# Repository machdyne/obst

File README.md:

# Obst Computer

Obst is an FPGA computer designed by Lone Dynamics Corporation.

This repo will contain schematics, PCB layouts, pinouts, a 3D-printable case, example gateware and documentation.

Find more information on the [Obst product page](https://machdyne.com/product/obst-computer/).

## Programming Obst

Obst has a JTAG interface and ships with a [DFU bootloader](https://github.com/machdyne/tinydfu-bootloader) that allows the included flash [MMOD](https://machdyne.com/product/mmod) to be programmed over the USB-C port.

### DFU

The DFU bootloader is available for 5 seconds after power-on, issuing a DFU command during this period will stop the boot process until the DFU device is detached. If no command is received the boot process will continue and the user gateware will be loaded.

Install [dfu-util](http://dfu-util.sourceforge.net) (Debian/Ubuntu):

```
$ sudo apt install dfu-util
```

Update the user gateware on the flash MMOD:

```
$ sudo dfu-util -a 0 -D image.bit
```

Detach the DFU device and continue the boot process:

```
$ sudo dfu-util -a 0 -e
```

It is possible to update the bootloader itself using DFU but you shouldn't attempt this unless you have a JTAG programmer (or another method to program the MMOD) available, in case you need to restore the bootloader.

### JTAG

These examples assume you're using a "USB Blaster" JTAG cable, see the header pinout below. You will need to have [openFPGALoader](https://github.com/trabucayre/openFPGALoader) installed.

Program the configuration SRAM:

```
openFPGALoader -c usb-blaster image.bit
```

Program the flash MMOD:

```
openFPGALoader -f -c usb-blaster images/bootloader/tinydfu_obst.bit
```

## Blinky 

Building the blinky example requires [Yosys](https://github.com/YosysHQ/yosys), [nextpnr-ecp5](https://github.com/YosysHQ/nextpnr) and [Project Trellis](https://github.com/YosysHQ/prjtrellis).

Assuming they are installed, you can simply type `make` to build the gateware, which will be written to output/blinky.bin. You can then use [openFPGALoader](https://github.com/trabucayre/openFPGALoader) or dfu-util to write the gateware to the device.

## Zucker SOC

Obst can be used with [Zucker SOC](https://github.com/machdyne/zucker).

## JTAG Header

The 3.3V JTAG header can be used to program the FPGA SRAM as well as the MMOD flash memory. It can also be used to provide power (5V) to the board.

```
2 4 6
1 3 5
```

| Pin | Signal |
| --- | ------ |
| 1 | TCK |
| 2 | TDI |
| 3 | TDO |
| 4 | TMS |
| 5 | 5V0 |
| 6 | GND |

## Board Revisions

| Revision | Notes |
| -------- | ----- |
| V0A | Initial production version |
| V0B | Latest production version |

## License

The contents of this repo are released under the [Lone Dynamics Open License](LICENSE.md) with the following exceptions:

- The KiCad design files contain parts of the [kicad-pmod](https://github.com/mithro/kicad-pmod) library which is released under the [Apache License, Version 2.0](https://www.apache.org/licenses/LICENSE-2.0.html).

- The KiCad design files may contain symbols and footprints released under other licenses; please contact us if we've failed to give proper attribution.

Note: You can use these designs for commercial purposes but we ask that instead of producing exact clones, that you either replace our trademarks and logos with your own or add your own next to ours.

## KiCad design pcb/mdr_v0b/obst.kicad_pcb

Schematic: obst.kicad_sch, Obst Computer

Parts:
C1, C2, C3, C4, C5, C6, C7, C9, C10, C32: 220nF; C_0603_1608Metric
C8, C11, C12, C13: 1uF; C_0603_1608Metric
C14, C15, C16, C33, C34, C35, C36: 4.7uF; C_0603_1608Metric
C17, C19, C21, C23, C25, C26, C29, C30: 100nF; C_0603_1608Metric
C18, C20, C22, C24: 2.2uF; C_0603_1608Metric
C27, C28, C31, C41: 10uF; C_0603_1608Metric
C37, C38: 10pF; C_0603_1608Metric
C39, C40, C42, C43: 22uF; C_0603_1608Metric
D2: LED_RGB_ANODE; LED_RGB_0606_CHANZON
FB1, FB2: Ferrite_Bead; R_0603_1608Metric
H1, H2, H3, H4: MountingHole_Pad; MountingHole_3.2mm_M3_Pad
J1: TYPE-C-31-M-12-FIXED; USB_C_Receptacle_HRO_TYPE-C-31-M-12-BIG-PADS; PARTREV A
J2: USB_A_Stacked; USB_A_Wuerth_61400826021_Horizontal_Stacked
J3: MICROSD; SDCARD
J4: AudioJack4; Jack_3.5mm_PJ320D_Horizontal
J5: Conn_02x03_Odd_Even; PinHeader_2x03_P2.54mm_Vertical
L1, L2: INDUCTOR; L_0805_2012Metric
MMOD1: PMOD-Device-x1-Type-2-SPI; MMOD_Host_Socket
PMOD1, PMOD2: PMOD-Device-x2-Type-1A-GPIO; PMOD_2x06_HOST
Q1, Q2, Q3, Q4: BSS138; SOT-323_SC-70
R2, R3, R12, R13, R14, R15: 4K7; R_0603_1608Metric
R4, R9: 5K1; R_0603_1608Metric
R5, R42, R51, R64, R69: 1K; R_0603_1608Metric
R6, R7, R20, R21, R22, R23: 22R; R_0603_1608Metric
R8: 51R; R_0603_1608Metric
R10, R11, R24, R27, R28, R29, R30, R33, R34, R35: 10K; R_0603_1608Metric
R16, R17, R18, R19: 15K; R_0603_1608Metric
R25, R26, R31, R32, R46, R52, R56, R57, R65, R70, R72, R73: 100R; R_0603_1608Metric
R36, R41, R48, R49, R50, R63, R68: 536R; R_0603_1608Metric
R37, R38, R39, R45: 20K; R_0603_1608Metric
R40, R53, R55, R67: 270R; R_0603_1608Metric
R43: 2K2; R_0603_1608Metric
R44, R58: 1K5; R_0603_1608Metric
R47: 33R; R_0603_1608Metric
R54, R66, R71: 27R; R_0603_1608Metric
R59: 100K; R_0603_1608Metric
R60: 120K; R_0603_1608Metric
R61: 200K; R_0603_1608Metric
R62: 44.2K; R_0603_1608Metric
TP1: TP_PWR5V0; TestPoint_THTPad_D1.0mm_Drill0.5mm
TP2: TP_PWR3V3; TestPoint_THTPad_D1.0mm_Drill0.5mm
TP3: TP_PWR1V1; TestPoint_THTPad_D1.0mm_Drill0.5mm
U1: Lattice_ECP_FPGA_ECP5U_45_CABGA256; BGA-256_14.0x14.0mm_Layout16x16_P0.8mm_Ball0.45mm_Pad0.32mm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
U2, U4: IS61WV51216EDBLL; TSOP-II-44_10.16x18.41mm_P0.8mm
U3, U5: PS2; MINI-DIN-6-FULL-SHIELD
U6: MIC5504-2.5YM5; SOT-23-5
U8, U9: TLV62568DDC; SOT-23-6
VGA1: DB15_Female_MountingHoles; DSUB-15-HD_Female_Horizontal_P2.29x1.98mm_EdgePinOffset3.03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
Y1: KC2016Z48.0000C1KX00; OSC_KC2016Z13.5600C1KX00; PARTREV November 2020

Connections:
/AUDIO_L: R72.1, U1.J2 (PL32B/-/PCLKC7_1/HS/LDQ29)
/AUDIO_LC: C27.2, J4.T
/AUDIO_R: R73.1, U1.J1 (PL32A/+/PCLKT7_1/HS/LDQ29)
/AUDIO_RC: C31.2, J4.R1
/CLK48: U1.A7 (PT38A/+/PCLKT0_0), Y1.3 (OUTPUT)
/CSPI_MISO: MMOD1.3 (MISO), R11.2, U1.T7 (PB11A/+/D1/MISO/IO1)
/CSPI_MOSI: MMOD1.2 (MOSI), R10.2, U1.T8 (PB11B/-/D0/MOSI/IO0)
/CSPI_SCK: MMOD1.4 (SCK), R5.2, U1.N9 (CCLK/MCLK/SCK)
/CSPI_SS: MMOD1.1 (SS), U1.N8 (PB15A/+/HOLDN/DI/BUSY/CSSPIN/CEN)
/DONE: U1.P9 (DONE)
/INITN: R2.2, U1.T9 (INITN)
/JTAG_TCK: J5.1, R15.1, U1.T10 (TCK)
/JTAG_TDI: J5.2, R12.2, U1.R11 (TDI)
/JTAG_TDO: J5.3, R13.2, U1.M10 (TDO)
/JTAG_TMS: J5.4, R14.2, U1.T11 (TMS)
/LED_B: R49.1, U1.B11 (PT58A/+)
/LED_G: R36.1, U1.A11 (PT71A/+)
/LED_R: R48.1, U1.C12 (PT74B/-)
/PMOD_A1: PMOD1.1 (IOA0), U1.E5 (PT13A/+)
/PMOD_A2: PMOD1.2 (IOA1), U1.D4 (PT9B/-)
/PMOD_A3: PMOD1.3 (IOA2), U1.B5 (PT15B/-)
/PMOD_A4: PMOD1.4 (IOA3), U1.C6 (PT31A/+)
/PMOD_A7: PMOD1.7 (IOB0), U1.E4 (PT9A/+)
/PMOD_A8: PMOD1.8 (IOB1), U1.C4 (PT11A/+)
/PMOD_A9: PMOD1.9 (IOB2), U1.B6 (PT31B/-)
/PMOD_A10: PMOD1.10 (IOB3), U1.D6 (PT20B/-)
/PMOD_B1: PMOD2.1 (IOA0), U1.C8 (PT44A/+/PCLKT1_0)
/PMOD_B2: PMOD2.2 (IOA1), U1.B9 (PT47A/+/GR_PCLK1_0)
/PMOD_B3: PMOD2.3 (IOA2), U1.A10 (PT51B/-)
/PMOD_B4: PMOD2.4 (IOA3), U1.C10 (PT53B/-)
/PMOD_B7: PMOD2.7 (IOB0), U1.B8 (PT44B/-/PCLKC1_0)
/PMOD_B8: PMOD2.8 (IOB1), U1.A9 (PT51A/+)
/PMOD_B9: PMOD2.9 (IOB2), U1.B10 (PT53A/+)
/PMOD_B10: PMOD2.10 (IOB3), U1.D10 (PT56A/+)
/PROGRAMN: R3.2, R8.2, U1.R9 (PROGRAMN)
/PS2A_CLK: Q2.2 (S), R28.2, U1.L2 (PL35B/-/PCLKC6_1/HS/LDQ41)
/PS2A_CLK5V: Q2.3 (D), R26.1, R29.2
/PS2A_DAT: Q1.2 (S), R24.2, U1.L1 (PL35A/+/PCLKT6_1/HS/LDQ41)
/PS2A_DAT5V: Q1.3 (D), R25.1, R27.2
/PS2B_CLK: Q4.2 (S), R34.2, U1.L4 (PL38C/+/GR_PCLK6_1/LDQ41)
/PS2B_CLK5V: Q4.3 (D), R32.1, R35.2
/PS2B_DAT: Q3.2 (S), R30.2, U1.L3 (PL41C/+/LDQ41)
/PS2B_DAT5V: Q3.3 (D), R31.1, R33.2
/PWR1V1: C3.2, C5.2, C10.2, C12.2, C13.2, C15.2, C37.1, C39.1, C40.1, C42.1, L1.2, R59.1, TP3.1, U1.G6 (VCC[6]), U1.G7 (VCC[6]), U1.G9 (VCC[6]), U1.L8 (VCC[6]), U1.L9 (VCC[6]), U1.L10 (VCC[6])
/PWR1V1EN: R58.2, U8.1 (EN), U9.5 (PG)
/PWR2V5: C4.2, C32.2, C34.1, U1.G11 (VCCAUX[2]), U1.L7 (VCCAUX[2]), U6.5 (VOUT)
/PWR3V3: C1.2, C2.2, C6.2, C7.2, C8.2, C9.2, C11.2, C17.2, C18.2, C19.2, C20.2, C21.2, C22.2, C23.2, C24.2, C25.1, C28.1, C29.1, C33.1, C38.1, C41.1, C43.1, D2.1 (A), J3.4 (VDD), L2.2, MMOD1.6 (VCC), PMOD1.6 (VCC), PMOD1.12 (VCC), PMOD2.6 (VCC), PMOD2.12 (VCC), Q1.1 (G), Q2.1 (G), Q3.1 (G), Q4.1 (G), R2.1, R3.1, R5.1, R10.1, R11.1, R12.1, R13.1, R14.1, R24.1, R28.1, R30.1, R34.1, R37.1, R38.1, R39.1, R45.1, R61.1, TP2.1, U1.F6 (VCCIO0[2]), U1.F7 (VCCIO0[2]), U1.F10 (VCCIO1[2]), U1.F11 (VCCIO1[2]), U1.H6 (VCCIO7[2]), U1.H7 (VCCIO7[2]), U1.H11 (VCCIO2[2]), U1.J6 (VCCIO6[2]), U1.J7 (VCCIO6[2]), U1.J11 (VCCIO2[2]), U1.K11 (VCCIO3[2]), U1.L6 (VCCIO8), U1.L11 (VCCIO3[2]), U1.P10 (CFG_1), U2.11 (VDD1), U2.33 (VDD2), U4.11 (VDD1), U4.33 (VDD2), U6.1 (VIN), U6.3 (EN), Y1.1 (INH), Y1.4 (VCC)
/PWR5V0: C14.1, C16.1, C35.1, C36.1, FB1.1, FB2.1, J5.5, R27.1, R29.1, R33.1, R35.1, R58.1, TP1.1, U3.4 (VCC), U5.4 (VCC), U8.4 (VIN), U9.1 (EN), U9.4 (VIN)
/RESET: R8.1, U1.M8 (PB15B/-/DOUT/CSON)
/SD_MISO: J3.7 (DAT0), R45.2, U1.B4 (PT11B/-)
/SD_MOSI: J3.3 (CMD), R38.2, U1.B3 (PT4B/-/ULC_GPLL1C_IN)
/SD_SCK: J3.5 (CLK), R39.2, U1.A3 (PT6A/+)
/SD_SS: J3.2 (DAT3/CD), R37.2, U1.A2 (PT4A/+/ULC_GPLL1T_IN)
/SRAM0_CS: U1.G12 (PR20A/+/HS/RDQ17), U4.6 (~CS)
/SRAM0_D0: U1.F12 (PR17D/-/RDQ17), U4.7 (D0)
/SRAM0_D1: U1.E14 (PR14C/+/RDQ17), U4.8 (D1)
/SRAM0_D2: U1.K15 (PR32D/-/PCLKC2_0/RDQ29), U4.9 (D2)
/SRAM0_D3: U1.K16 (PR32C/+/PCLKT2_0/RDQ29), U4.10 (D3)
/SRAM0_D4: U1.J15 (PR32B/-/PCLKC2_1/HS/RDQ29), U4.13 (D4)
/SRAM0_D5: U1.J16 (PR32A/+/PCLKT2_1/HS/RDQ29), U4.14 (D5)
/SRAM0_D6: U1.H14 (PR23D/-/RDQ29), U4.15 (D6)
/SRAM0_D7: U1.H15 (PR29B/-/HS/RDQSN29), U4.16 (D7)
/SRAM0_D8: U1.G15 (PR23B/-/HS/RDQ29), U4.29 (D8)
/SRAM0_D9: U1.F16 (PR23A/+/HS/RDQ29), U4.30 (D9)
/SRAM0_D10: U1.F15 (PR20C/+/RDQ17), U4.31 (D10)
/SRAM0_D11: U1.E16 (PR20D/-/RDQ17), U4.32 (D11)
/SRAM0_D12: U1.E15 (PR17B/-/HS/RDQSN17), U4.35 (D12)
/SRAM0_D13: U1.D16 (PR17A/+/HS/RDQS17), U4.36 (D13)
/SRAM0_D14: U1.C14 (PR11C/+/RDQ17), U4.37 (D14)
/SRAM0_D15: U1.C16 (PR14A/+/HS/RDQ17), U4.38 (D15)
/SRAM0_LB: U1.C15 (PR14B/-/HS/RDQ17), U4.39 (~LB)
/SRAM0_OE: U1.B15 (PR11B/-/URC_GPLL0C_IN/HS/RDQ17), U4.41 (~OE)
/SRAM0_UB: U1.B16 (PR11A/+/URC_GPLL0T_IN/HS/RDQ17), U4.40 (~UB)
/SRAM0_WE: U1.G16 (PR29A/+/GR_PCLK2_1/HS/RDQS29), U4.17 (~WE)
/SRAM1_CS: U1.L12 (PR38D/-/RDQ41), U2.6 (~CS)
/SRAM1_D0: U1.L13 (PR38C/+/GR_PCLK3_1/RDQ41), U2.7 (D0)
/SRAM1_D1: U1.L14 (PR41C/+/RDQ41), U2.8 (D1)
/SRAM1_D2: U1.M13 (PR44C/+/RDQ41), U2.9 (D2)
/SRAM1_D3: U1.P11 (PR68C/+/LRC_GPLL0T_IN/RDQ65), U2.10 (D3)
/SRAM1_D4: U1.R12 (PR65A/+/HS/RDQS65), U2.13 (D4)
/SRAM1_D5: U1.T13 (PR65B/-/HS/RDQSN65), U2.14 (D5)
/SRAM1_D6: U1.R13 (PR62C/+/RDQ65), U2.15 (D6)
/SRAM1_D7: U1.T14 (PR62D/-/RDQ65), U2.16 (D7)
/SRAM1_D8: U1.T15 (PR59D/-/RDQ65), U2.29 (D8)
/SRAM1_D9: U1.R15 (PR59C/+/RDQ65), U2.30 (D9)
/SRAM1_D10: U1.R16 (PR44B/-/VREF1_3/HS/RDQ41), U2.31 (D10)
/SRAM1_D11: U1.P15 (PR41B/-/HS/RDQSN41), U2.32 (D11)
/SRAM1_D12: U1.P16 (PR44A/+/HS/RDQ41), U2.35 (D12)
/SRAM1_D13: U1.N14 (PR44D/-/RDQ41), U2.36 (D13)
/SRAM1_D14: U1.N16 (PR41A/+/HS/RDQS41), U2.37 (D14)
/SRAM1_D15: U1.L16 (PR35A/+/PCLKT3_1/HS/RDQ41), U2.38 (D15)
/SRAM1_LB: U1.L15 (PR35B/-/PCLKC3_1/HS/RDQ41), U2.39 (~LB)
/SRAM1_OE: U1.M15 (PR35D/-/PCLKC3_0/RDQ41), U2.41 (~OE)
/SRAM1_UB: U1.M16 (PR35C/+/PCLKT3_0/RDQ41), U2.40 (~UB)
/SRAM1_WE: U1.R14 (PR62B/-/HS/RDQ65), U2.17 (~WE)
/SRAM_A0: U1.J14 (PR29C/+/GR_PCLK2_0/RDQ29), U2.1 (A0), U4.1 (A0)
/SRAM_A1: U1.J13 (PR26C/+/RDQ29), U2.2 (A1), U4.2 (A1)
/SRAM_A2: U1.J12 (PR26D/-/RDQ29), U2.3 (A2), U4.3 (A2)
/SRAM_A3: U1.G14 (PR23C/+/VREF1_2/RDQ29), U2.4 (A3), U4.4 (A3)
/SRAM_A4: U1.G13 (PR20B/-/HS/RDQ17), U2.5 (A4), U4.5 (A4)
/SRAM_A5: U1.N13 (PR59A/+/HS/RDQ65), U2.18 (A5), U4.18 (A5)
/SRAM_A6: U1.P14 (PR59B/-/HS/RDQ65), U2.19 (A6), U4.19 (A6)
/SRAM_A7: U1.P13 (PR62A/+/HS/RDQ65), U2.20 (A7), U4.20 (A7)
/SRAM_A8: U1.P12 (PR68D/-/LRC_GPLL0C_IN/RDQ65), U2.21 (A8), U4.21 (A8)
/SRAM_A9: U1.N12 (PR65D/-/RDQ65), U2.22 (A9), U4.22 (A9)
/SRAM_A10: U1.B12 (PT74A/+), U2.23 (A10), U4.23 (A10)
/SRAM_A11: U1.A12 (PT71B/-), U2.24 (A11), U4.24 (A11)
/SRAM_A12: U1.A13 (PT83A/+), U2.25 (A12), U4.25 (A12)
/SRAM_A13: U1.B13 (PT78A/+), U2.26 (A13), U4.26 (A13)
/SRAM_A14: U1.C13 (PT78B/-), U2.27 (A14), U4.27 (A14)
/SRAM_A15: U1.A15 (PT85B/-/URC_GPLL1C_IN), U2.42 (A15), U4.42 (A15)
/SRAM_A16: U1.B14 (PT85A/+/URC_GPLL1T_IN), U2.43 (A16), U4.43 (A16)
/SRAM_A17: U1.A14 (PT83B/-), U2.44 (A17), U4.44 (A17)
/SRAM_A18: U1.D13 (PT80A/+), U2.28 (A18), U4.28 (A18)
/USB1C_DN: J2.2 (D1-), R17.1, R21.2
/USB1C_DP: J2.3 (D1+), R16.1, R20.2
/USB1_DN: R21.1, U1.B2 (PL11B/-/ULC_GPLL0C_IN/HS/LDQ17)
/USB1_DP: R20.1, U1.B1 (PL11A/+/ULC_GPLL0T_IN/HS/LDQ17)
/USB2C_DN: J2.6 (D2-), R19.1, R23.2
/USB2C_DP: J2.7 (D2+), R18.1, R22.2
/USB2_DN: R23.1, U1.C2 (PL14B/-/HS/LDQ17)
/USB2_DP: R22.1, U1.C1 (PL14A/+/HS/LDQ17)
/USB_CONN_DN: J1.A7 (DN1), J1.B7 (DN2), R6.1
/USB_CONN_DP: J1.A6 (DP1), J1.B6 (DP2), R7.1
/USB_DN: R6.2, U1.M2 (PL35D/-/PCLKC6_0/LDQ41)
/USB_DP: R7.2, R44.2, U1.M1 (PL35C/+/PCLKT6_0/LDQ41)
/USB_DP_PU: R44.1, U1.R1 (PL44B/-/VREF1_6/HS/LDQ41)
/VGA_B0: R67.2, U1.N3 (PL44D/-/LDQ41)
/VGA_B1: R68.2, U1.T2 (PL59D/-/LDQ65)
/VGA_B2: R69.2, U1.R2 (PL59C/+/LDQ65)
/VGA_B_CONN: R71.1, VGA1.3
/VGA_G0: R55.2, U1.T4 (PL65B/-/HS/LDQSN65)
/VGA_G1: R63.2, U1.R4 (PL62C/+/LDQ65)
/VGA_G2: R64.2, U1.P4 (PL62A/+/HS/LDQ65)
/VGA_G_CONN: R66.1, VGA1.2
/VGA_HS: R56.2, U1.P2 (PL41B/-/HS/LDQSN41)
/VGA_HS_CONN: R56.1, VGA1.13
/VGA_R0: R53.2, U1.M6 (PL68A/+/HS/LDQ65)
/VGA_R1: R50.2, U1.P6 (PL68C/+/LLC_GPLL0T_IN/LDQ65)
/VGA_R2: R51.2, U1.N6 (PL68B/-/HS/LDQ65)
/VGA_R_CONN: R54.1, VGA1.1
/VGA_VS: R57.2, U1.N1 (PL41A/+/HS/LDQS41)
/VGA_VS_CONN: R57.1, VGA1.14
/VIDEOC: J4.R2, R47.2
/VIDEO_D0: R40.1, U1.G4 (PL20B/-/HS/LDQ17)
/VIDEO_D1: R41.1, U1.G3 (PL23C/+/VREF1_7/LDQ29)
/VIDEO_D2: R42.1, U1.G2 (PL23B/-/HS/LDQ29)
/VIDEO_D3: R43.1, U1.H2 (PL29B/-/HS/LDQSN29)
GND: C1.1, C2.1, C3.1, C4.1, C5.1, C6.1, C7.1, C8.1, C9.1, C10.1, C11.1, C12.1, C13.1, C14.2, C15.1, C16.2, C17.1, C18.1, C19.1, C20.1, C21.1, C22.1, C23.1, C24.1, C25.2, C26.2, C28.2, C29.2, C30.2, C32.1, C33.2, C34.2, C35.2, C36.2, C39.2, C40.2, C41.2, C42.2, C43.2, H1.1, H2.1, H3.1, H4.1, J1.A1 (GND), J1.A12 (GND), J1.B1 (GND), J1.B12 (GND), J1.S1 (SHIELD), J1.S2 (SHIELD), J1.S3 (SHIELD), J1.S4 (SHIELD), J2.4 (GND1), J2.8 (GND2), J2.9 (Shield), J3.6 (VSS), J4.S, J5.6, MMOD1.5 (GND), PMOD1.5 (GND), PMOD1.11 (GND), PMOD2.5 (GND), PMOD2.11 (GND), R4.2, R9.2, R15.2, R16.2, R17.2, R18.2, R19.2, R60.2, R62.2, U1.A1 (GND[27]), U1.A16 (GND[27]), U1.D2 (GND[27]), U1.D15 (GND[27]), U1.F8 (GND[27]), U1.F9 (GND[27]), U1.G8 (GND[27]), U1.G10 (GND[27]), U1.H1 (GND[27]), U1.H8 (GND[27]), U1.H9 (GND[27]), U1.H10 (GND[27]), U1.H16 (GND[27]), U1.J8 (GND[27]), U1.J9 (GND[27]), U1.J10 (GND[27]), U1.K6 (GND[27]), U1.K7 (GND[27]), U1.K8 (GND[27]), U1.K9 (GND[27]), U1.K10 (GND[27]), U1.N2 (GND[27]), U1.N10 (CFG_0), U1.N15 (GND[27]), U1.R10 (CFG_2), U1.T1 (GND[27]), U1.T5 (GND[27]), U1.T12 (GND[27]), U1.T16 (GND[27]), U2.12 (VSS1), U2.34 (VSS2), U3.3 (GND), U4.12 (VSS1), U4.34 (VSS2), U5.3 (GND), U6.2 (GND), U8.2 (GND), U9.2 (GND), VGA1.0 (PAD), VGA1.5, VGA1.6, VGA1.7, VGA1.8, VGA1.10, Y1.2 (CASE_GND)
unnamed: C26.1, C27.1, R72.2
unnamed: C30.1, C31.1, R73.2
unnamed: D2.2 (BK), R49.2
unnamed: D2.4 (GK), R36.2
unnamed: D2.3 (RK), R48.2
unnamed: FB1.2, J1.A4 (VBUS), J1.A9 (VBUS), J1.B4 (VBUS), J1.B9 (VBUS)
unnamed: J1.A5 (CC1), R4.1
unnamed: J1.B5 (CC2), R9.1
unnamed: FB2.2, J2.1 (VBUS1), J2.5 (VBUS2)
unnamed: R40.2, R41.2, R42.2, R43.2, R46.1
unnamed: R46.2, R47.1
unnamed: R50.1, R51.1, R52.2, R53.1
unnamed: R52.1, R54.2
unnamed: R55.1, R63.1, R64.1, R65.2
unnamed: R65.1, R66.2
unnamed: R67.1, R68.1, R69.1, R70.2
unnamed: R70.1, R71.2
unnamed: R26.2, U3.5 (CLK)
unnamed: R25.2, U3.1 (DATA)
unnamed: R32.2, U5.5 (CLK)
unnamed: R31.2, U5.1 (DATA)
unnamed: C37.2, R59.2, R60.1, U8.6 (FB)
unnamed: L1.1, U8.3 (SW)
unnamed: C38.2, R61.2, R62.1, U9.6 (FB)
unnamed: L2.1, U9.3 (SW)

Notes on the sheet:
0.6 * (1 + (100/120)) = 1.099
PS/2
POWER
0.6 * (1 + (200/44.2)) = 3.3149
VGA DAC
MMOD has a 10K pull-up on CSPI_SS
MICROSD
USB DEVICE
AUDIO/VIDEO
USB HOST
MMOD
PMODS
32-BIT SRAM
O B S T

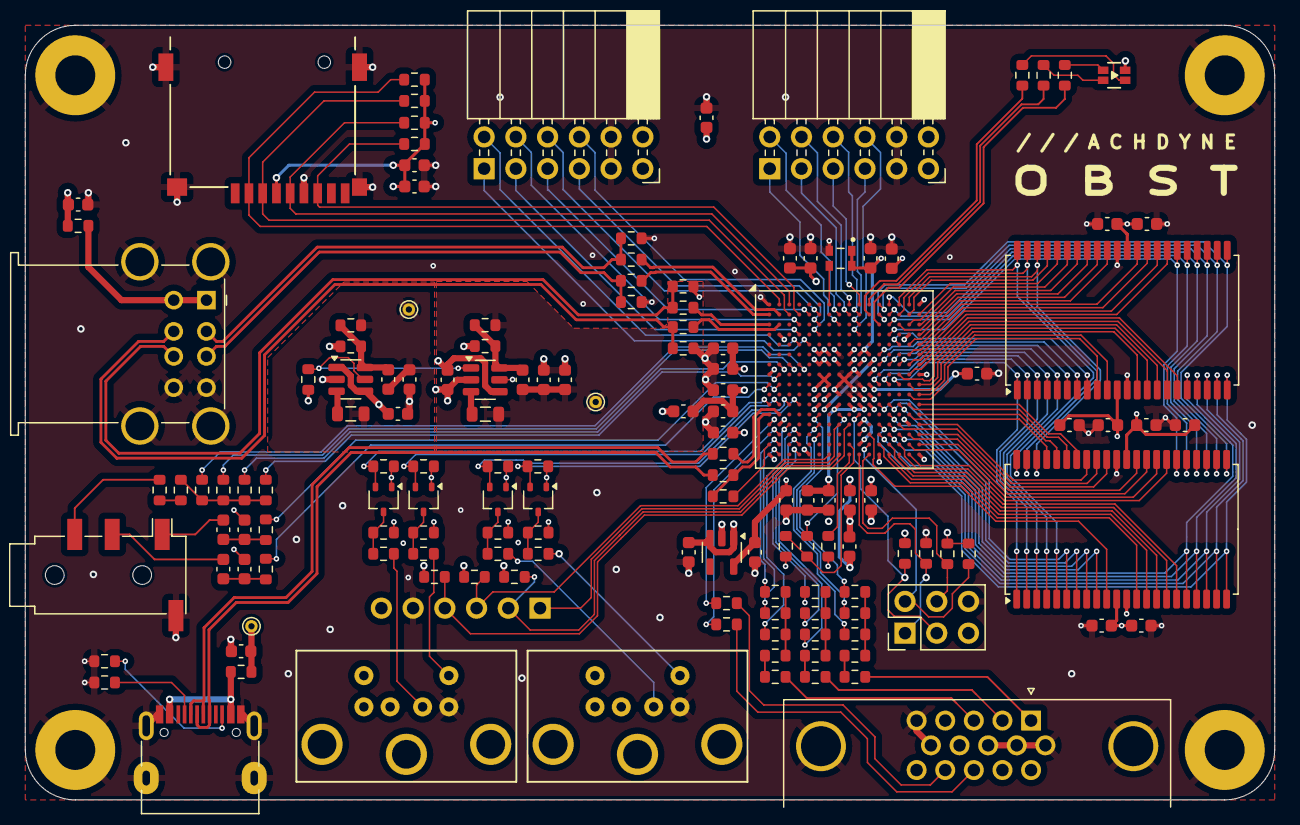
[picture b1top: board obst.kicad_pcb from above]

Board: 4 copper layers, 100.0 x 62.0 mm, 149 parts (1 on the bottom side), 173 nets.

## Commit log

2024-04-24 add render
2024-04-24 add bootloader image
2024-04-24 add blinky
2024-04-24 add constraints
2024-04-26 add case
2024-04-26 update case
2024-09-08 add pmods to lpf
2024-09-08 add audio/video to lpf
2024-09-08 add remaining signals to lpf
2024-10-17 add supports
2026-06-17 add schematics and pcb layout

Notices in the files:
pcb/mdr_v0b/obst.kicad_sch:
Copyright © 2024 Lone Dynamics Corporation
